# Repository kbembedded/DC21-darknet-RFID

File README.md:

DC21-darknet-RFID
=================

Note: This project is deprecated in favor of the EM4100_Cloner available here: https://github.com/kbembedded/EM4100_Cloner

Send any quesions to kris@kbembedded.com

Software, schematics, board, etc. for the DEF CON21 darknet ARG in the HHV

This project is based on the RFID_Emulator from http://www.kukata86.com/en/description-and-development-RFID-emulator

The RFID-emulator/ folder contains sources for the pic12f683 microcontroller to act as two types of LF RFID cards.  A standard EM4100, as well as EM4450/EM4150 to be compatible with the RFID reader and RFID reader/writer module from Parallax.  

The RFID-readerwriter/ folder contains spin sources for a Parallax reader/writer module connected to a Propeller, using a 4x4 matrix keypad interface, and an HD44780 LCD screen.

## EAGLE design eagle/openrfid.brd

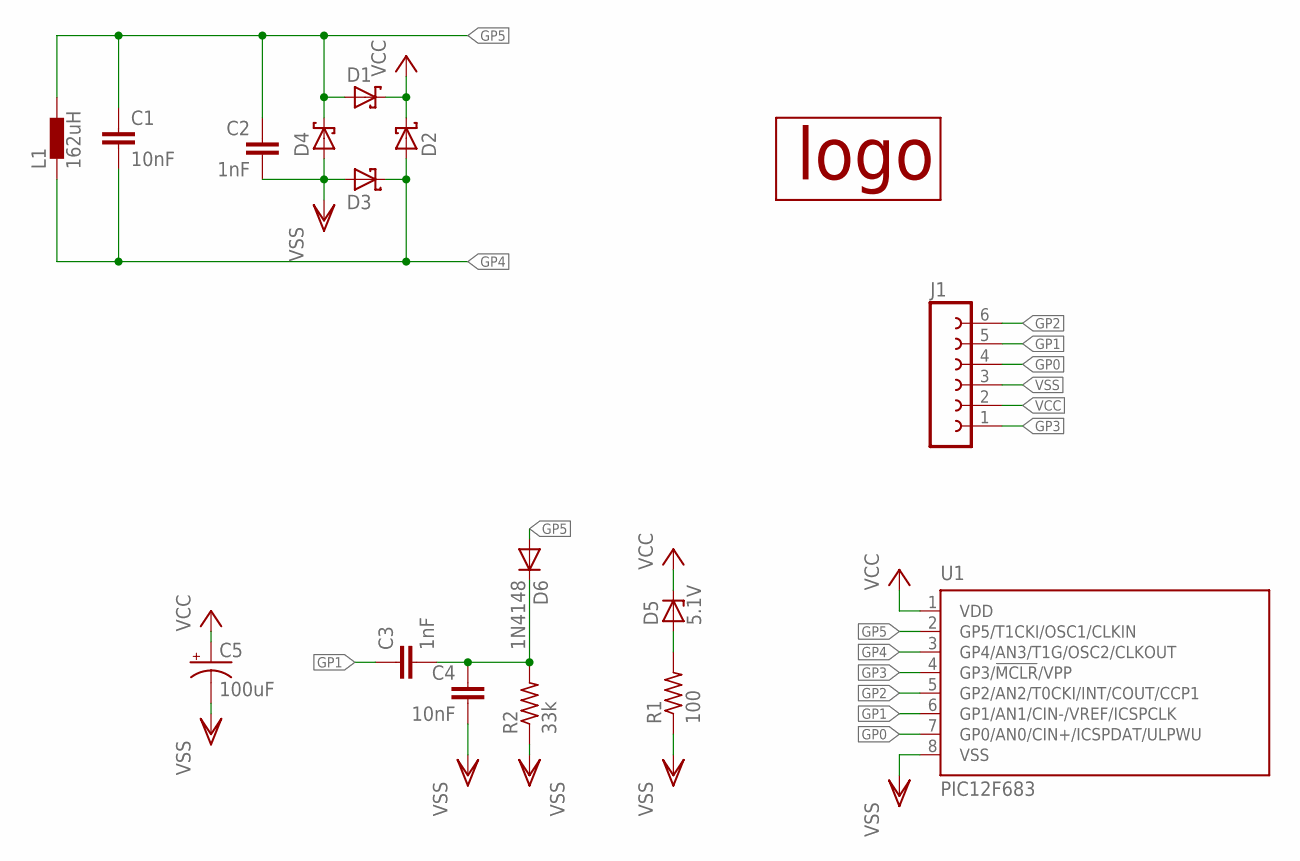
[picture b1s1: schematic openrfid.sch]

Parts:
C1, C4: 10nF; C050-024X044
C2, C3: 1nF; C025-024X044
C5: 100uF; E2,5-6E
D1, D2, D3, D4: 1N5817-B; DO41-7.6
D5: 5.1V; ZDIO-5
D6: 1N4148; DO35-7
J1: FE06-1; FE06
L1: 162uH; BL02RN2
R1: 100; 0204/7
R2: 33k; 0204/7
U1: PIC12F683; DIL8
U$1: KBELOGO-SILK

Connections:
GP0: J1.4, U1.7 (GP0/AN0/CIN+/ICSPDAT/ULPWU)
GP1: C3.1, J1.5, U1.6 (GP1/AN1/CIN-/VREF/ICSPCLK)
GP2: J1.6, U1.5 (GP2/AN2/T0CKI/INT/COUT/CCP1)
GP3: J1.1, U1.4 (GP3/!MCLR!/VPP)
GP4: C1.2, D2.A, D3.C, L1.1, U1.3 (GP4/AN3/T1G/OSC2/CLKOUT)
GP5: C1.1, C2.1, D1.A, D4.C, D6.A, L1.2, U1.2 (GP5/T1CKI/OSC1/CLKIN)
unnamed: D5.A, R1.2
unnamed: C3.2, C4.1, D6.C, R2.2
VCC: C5.+, D1.C, D2.C, D5.C, J1.2, U1.1 (VDD)
VSS: C2.2, C4.2, C5.-, D3.A, D4.A, J1.3, R1.1, R2.1, U1.8 (VSS)

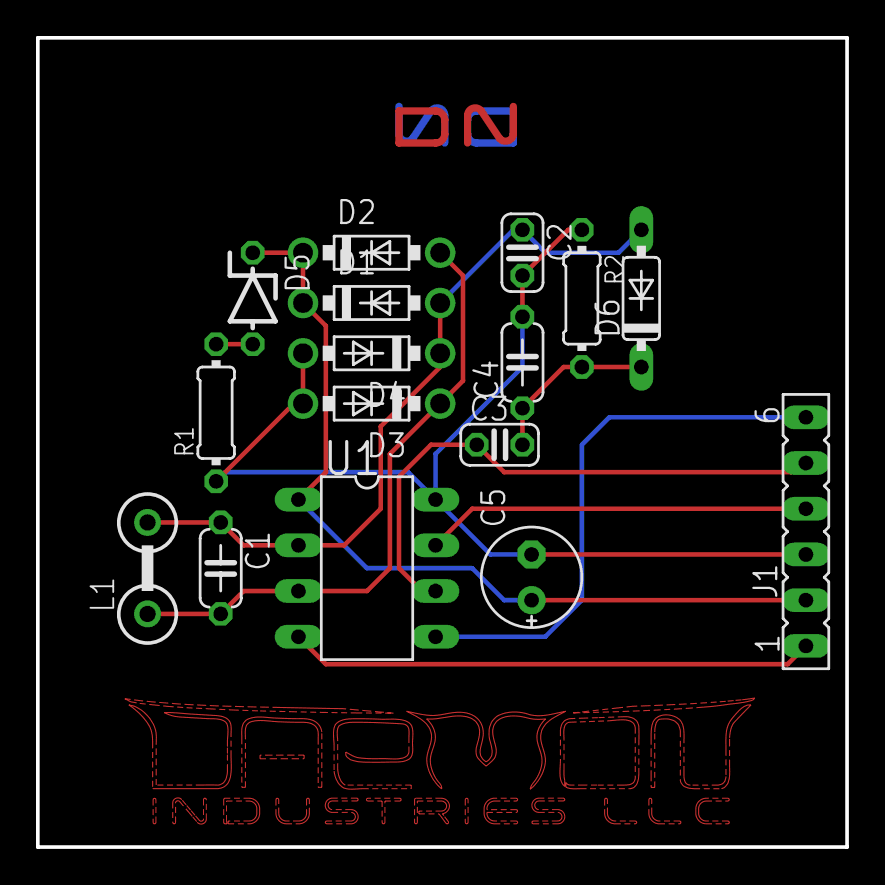
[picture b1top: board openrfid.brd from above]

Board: 2 copper layers, 45.0 x 45.0 mm, 17 parts (1 on the bottom side), 10 nets.

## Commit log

2013-07-17 Initial commit of sources, eagle cad, and docs for tag Initial commit of sources for custom reader/writer rig
2013-07-20 Add R/W Demo Code for bs2
    BS2 demo code for Parallax RFID reader-writer is added in
    ~\RFID-readerwriter\bs2\. Original source for propeller moved to
    ~\RFID-readerwriter\prop\.
2013-07-20 Add .gitignore
    Ignored directories labeled build/ or dist/ and .map files.
2013-07-20 Update BS2 Demo Code
    Pin choices and stamp header updated to match kris's awesome breadboard
    layout.
2013-07-20 Translate RFID Emulator Code into English
    RFID Emulator code is now in English. Coincidentally, I am now able to
    understand it.
    Special thanks to Semi-Pro Spanish Translator Cosima.
2013-07-20 Add Translations and Formatting
    Converted all tabs to spaces.
    Made a few more translations that were previously missed.
    Added comments to better describe what's happening.
2013-07-20 Update .gitignore
    Removes Mac generated garbage files and more build residue.
2013-07-23 Add BS2 RFID Reader Demo Code
    Parallax RFID Reader has separate demo code, plans are to use it as a
    starting point for creating validation code for changes made to the RFID
    emulator.
2013-07-24 Add RFID Printer code for Read Module
    Adds code for the reader module to print out the received RFID tag data.
    Also found the location of the RFID memory in the emulator code, added
    comments to it.
    Only strange thing is that the emulator is no longer readable if I
    change any of the data...
2013-07-25 Add User Manual
    Started on user manual for the event. Contains a bill of materials.
2013-07-26 Added Global RF routines to drive 1 or 0 for 1/2 bit time Added rough LIW function, tested and working Going to pass out now
2013-07-27 Update User Manual
    Noted optional components and added missing parts.
2013-07-30 Added/updated comments Force us in to not clone mode, since we dont have a button Changed EE_RFID_MEMORY default value Commented out all macros and definitions using button1, this PCB has no button P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
2013-07-30 Updated .gitignore to use correct project path
2013-07-30 Moved instructions to doc folder Added kit stickers to be printed on 3.9x6 paper
2013-07-30 Removed horrible docx format of instructions Added horrible odt format of instructions and PDF
2013-07-31 Fixed a description issue, bobbin cannot be used as a core Doesnt not have enough energy transfer
2013-07-31 Grammatical fixes Cleared up some info wiht the antenna design
2013-08-05 Updated readme to note hiatus
2014-02-25 Removed code protect from code
2015-08-11 Added deprecation note to README
